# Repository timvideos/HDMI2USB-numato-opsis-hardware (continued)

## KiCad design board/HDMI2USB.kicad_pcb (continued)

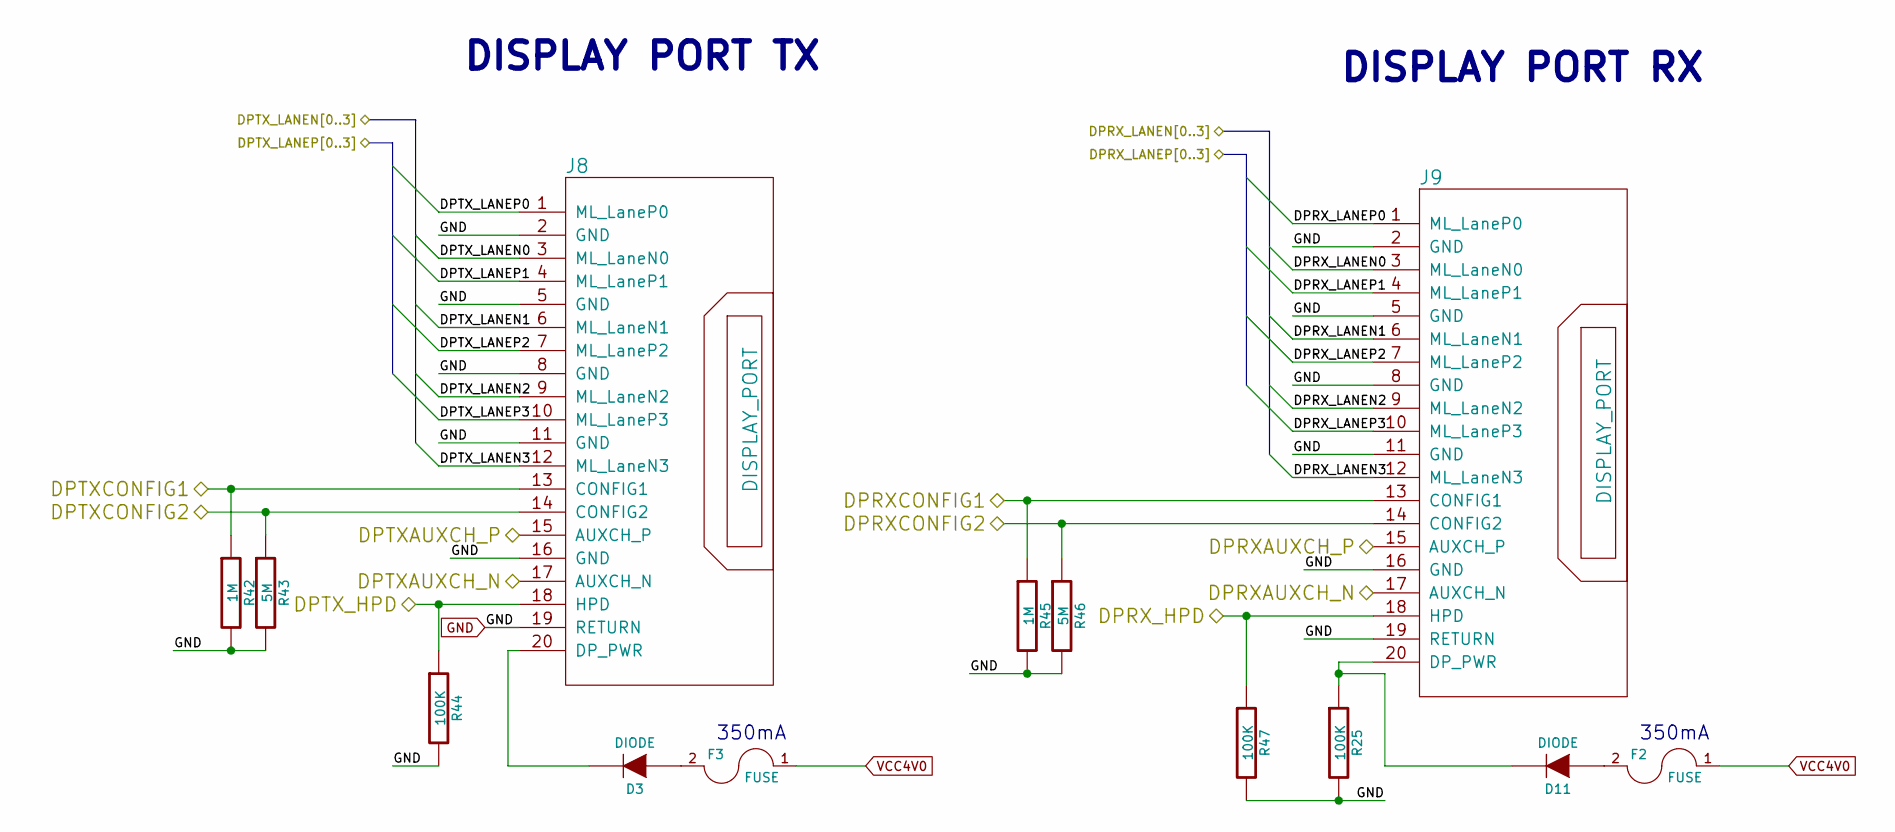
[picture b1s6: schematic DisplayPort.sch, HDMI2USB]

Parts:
D3, D11: DIODE
F2, F3: FUSE
J8, J9: DISPLAY_PORT
R25, R44, R47: 100K
R42, R45: 1M
R43, R46: 5M

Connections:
/DisplayPort/DPRXAUXCH_N: J9.17 (AUXCH_N); also elsewhere on the board
/DisplayPort/DPRXAUXCH_P: J9.15 (AUXCH_P); also elsewhere on the board
/DisplayPort/DPRXCONFIG1: J9.13 (CONFIG1), R45.1; also elsewhere on the board
/DisplayPort/DPRXCONFIG2: J9.14 (CONFIG2), R46.1; also elsewhere on the board
/DisplayPort/DPRX_LANEN0: J9.3 (ML_LaneN0); also elsewhere on the board
/DisplayPort/DPRX_LANEN1: J9.6 (ML_LaneN1); also elsewhere on the board
/DisplayPort/DPRX_LANEN2: J9.9 (ML_LaneN2); also elsewhere on the board
/DisplayPort/DPRX_LANEN3: J9.12 (ML_LaneN3); also elsewhere on the board
/DisplayPort/DPRX_LANEP0: J9.1 (ML_LaneP0); also elsewhere on the board
/DisplayPort/DPRX_LANEP1: J9.4 (ML_LaneP1); also elsewhere on the board
/DisplayPort/DPRX_LANEP2: J9.7 (ML_LaneP2); also elsewhere on the board
/DisplayPort/DPRX_LANEP3: J9.10 (ML_LaneP3); also elsewhere on the board
/DisplayPort/DPTXAUXCH_N: J8.17 (AUXCH_N); also elsewhere on the board
/DisplayPort/DPTXAUXCH_P: J8.15 (AUXCH_P); also elsewhere on the board
/DisplayPort/DPTXCONFIG1: J8.13 (CONFIG1), R42.1; also elsewhere on the board
/DisplayPort/DPTXCONFIG2: J8.14 (CONFIG2), R43.1; also elsewhere on the board
/DisplayPort/DPTX_LANEN0: J8.3 (ML_LaneN0); also elsewhere on the board
/DisplayPort/DPTX_LANEN1: J8.6 (ML_LaneN1); also elsewhere on the board
/DisplayPort/DPTX_LANEN2: J8.9 (ML_LaneN2); also elsewhere on the board
/DisplayPort/DPTX_LANEN3: J8.12 (ML_LaneN3); also elsewhere on the board
/DisplayPort/DPTX_LANEP0: J8.1 (ML_LaneP0); also elsewhere on the board
/DisplayPort/DPTX_LANEP1: J8.4 (ML_LaneP1); also elsewhere on the board
/DisplayPort/DPTX_LANEP2: J8.7 (ML_LaneP2); also elsewhere on the board
/DisplayPort/DPTX_LANEP3: J8.10 (ML_LaneP3); also elsewhere on the board
/FPGA_Bank_1_2/DPRXHPD: J9.18 (HPD), R47.1; also elsewhere on the board
/FPGA_Bank_1_2/DPTXHPD: J8.18 (HPD), R44.1; also elsewhere on the board
unnamed: D11.2 (K), J9.20 (DP_PWR), R25.1
unnamed: D3.1 (A), F3.2
unnamed: D3.2 (K), J8.20 (DP_PWR)

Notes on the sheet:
350mA
DISPLAY PORT TX
DISPLAY PORT RX

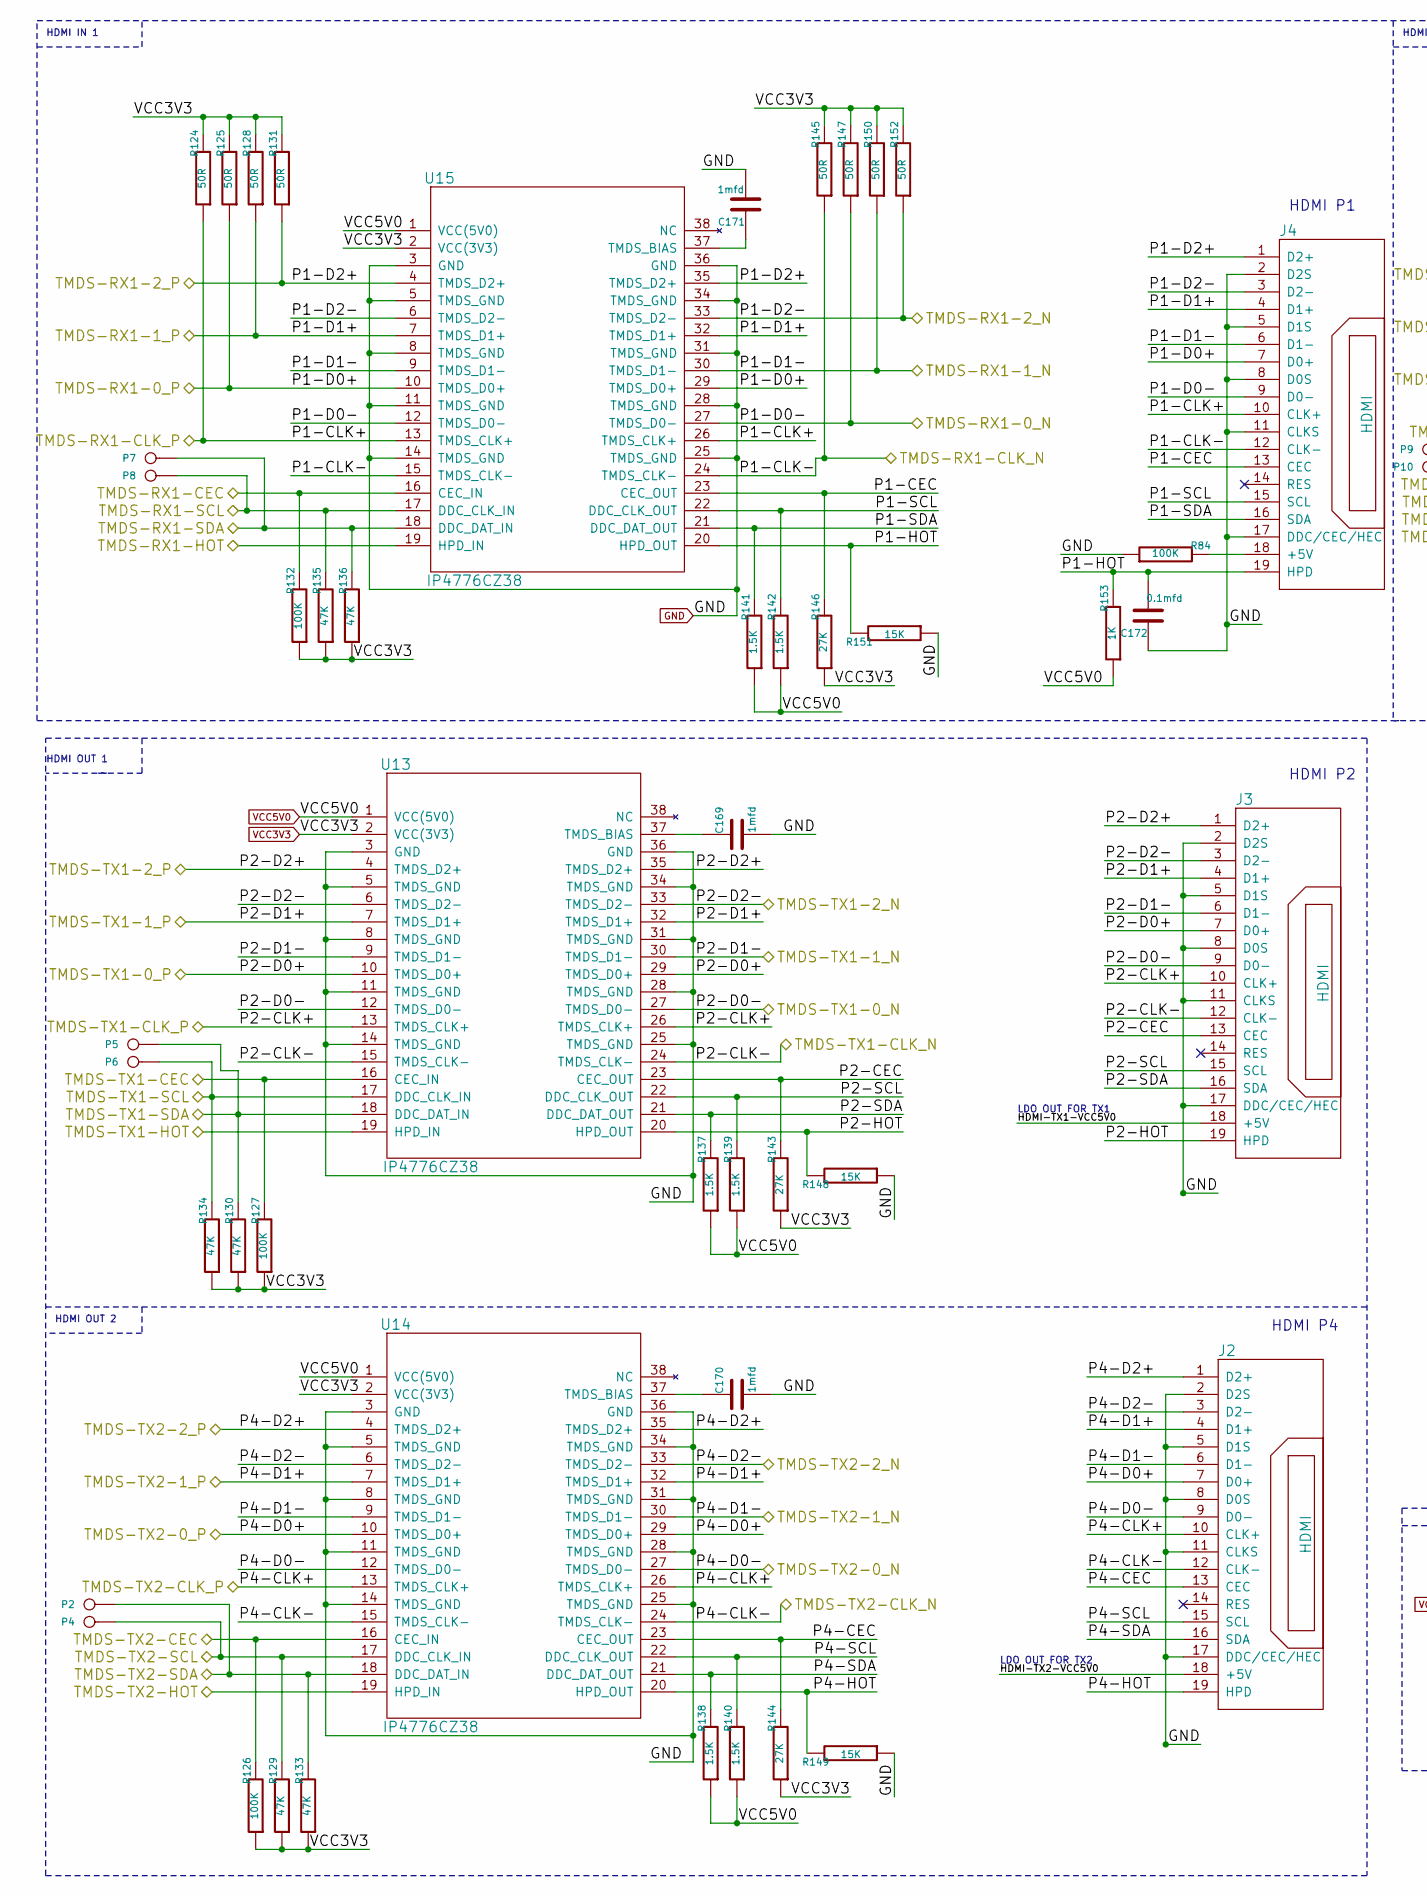
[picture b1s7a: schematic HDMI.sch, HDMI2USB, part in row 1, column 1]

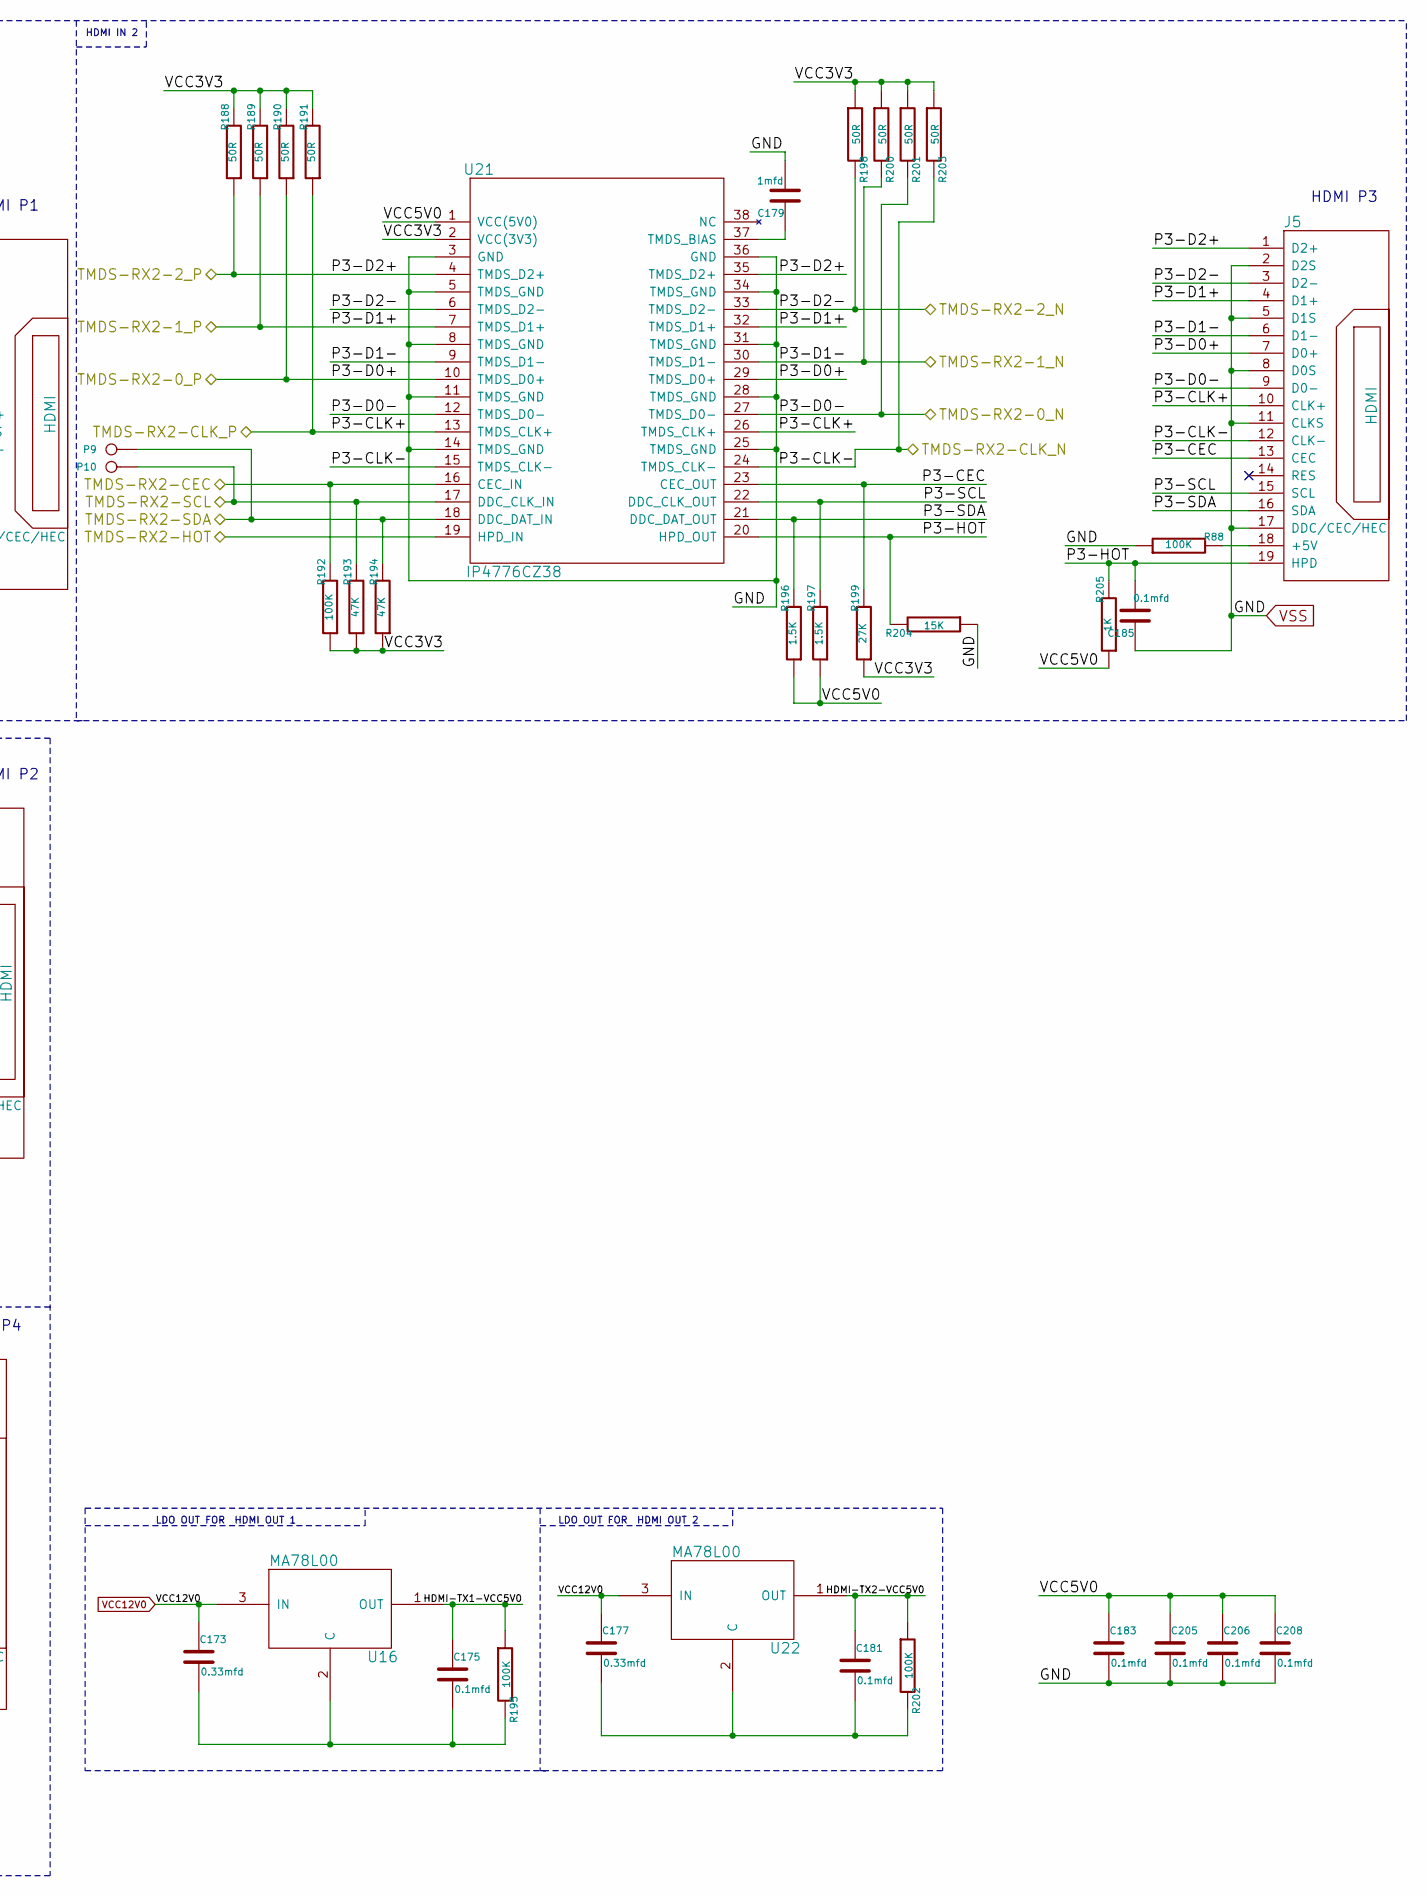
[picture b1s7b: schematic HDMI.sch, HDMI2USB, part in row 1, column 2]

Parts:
C169, C170, C171, C179: 1mfd
C172, C175, C181, C183, C185, C205, C206, C208: 0.1mfd
C173, C177: 0.33mfd
J2, J3, J4, J5: HDMI
P2, P4, P5, P6, P7, P8, P9, P10: CONN_1
R84, R88, R126, R127, R132, R192, R195, R202: 100K
R124, R125, R128, R131, R145, R147, R150, R152, R188, R189, R190, R191, R198, R200, R201, R203: 50R
R129, R130, R133, R134, R135, R136, R193, R194: 47K
R137, R138, R139, R140, R141, R142, R196, R197: 1.5K
R143, R144, R146, R199: 27K
R148, R149, R151, R204: 15K
R153, R205: 1K
U13, U14, U15, U21: IP4776CZ38
U16, U22: ΜA78L00

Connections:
/HDMI/HDMI-TX1-VCC5V0: C175.1, J3.18 (+5V), R195.1, U16.1 (OUT)
/HDMI/HDMI-TX2-VCC5V0: C181.1, J2.18 (+5V), R202.1, U22.1 (OUT)
/HDMI/P1-CEC: J4.13 (CEC), R146.2, U15.23 (CEC_OUT)
/HDMI/P1-HOT: C172.2, J4.19 (HPD), R151.2, R153.2, U15.20 (HPD_OUT)
/HDMI/P1-SCL: J4.15 (SCL), R142.2, U15.22 (DDC_CLK_OUT)
/HDMI/P1-SDA: J4.16 (SDA), R141.2, U15.21 (DDC_DAT_OUT)
/HDMI/P2-CEC: J3.13 (CEC), R143.2, U13.23 (CEC_OUT)
/HDMI/P2-HOT: J3.19 (HPD), R148.2, U13.20 (HPD_OUT)
/HDMI/P2-SCL: J3.15 (SCL), R139.2, U13.22 (DDC_CLK_OUT)
/HDMI/P2-SDA: J3.16 (SDA), R137.2, U13.21 (DDC_DAT_OUT)
/HDMI/P3-CEC: J5.13 (CEC), R199.2, U21.23 (CEC_OUT)
/HDMI/P3-HOT: C185.2, J5.19 (HPD), R204.2, R205.2, U21.20 (HPD_OUT)
/HDMI/P3-SCL: J5.15 (SCL), R197.2, U21.22 (DDC_CLK_OUT)
/HDMI/P3-SDA: J5.16 (SDA), R196.2, U21.21 (DDC_DAT_OUT)
/HDMI/P4-CEC: J2.13 (CEC), R144.2, U14.23 (CEC_OUT)
/HDMI/P4-HOT: J2.19 (HPD), R149.2, U14.20 (HPD_OUT)
/HDMI/P4-SCL: J2.15 (SCL), R140.2, U14.22 (DDC_CLK_OUT)
/HDMI/P4-SDA: J2.16 (SDA), R138.2, U14.21 (DDC_DAT_OUT)
/HDMI/TMDS-RX1-0_N: J4.9 (D0-), R147.1, U15.12 (TMDS_D0-), U15.27 (TMDS_D0-); also elsewhere on the board
/HDMI/TMDS-RX1-0_P: J4.7 (D0+), R125.1, U15.10 (TMDS_D0+), U15.29 (TMDS_D0+); also elsewhere on the board
/HDMI/TMDS-RX1-1_N: J4.6 (D1-), R150.1, U15.9 (TMDS_D1-), U15.30 (TMDS_D1-); also elsewhere on the board
/HDMI/TMDS-RX1-1_P: J4.4 (D1+), R128.1, U15.7 (TMDS_D1+), U15.32 (TMDS_D1+); also elsewhere on the board
/HDMI/TMDS-RX1-2_N: J4.3 (D2-), R152.1, U15.6 (TMDS_D2-), U15.33 (TMDS_D2-); also elsewhere on the board
/HDMI/TMDS-RX1-2_P: J4.1 (D2+), R131.1, U15.4 (TMDS_D2+), U15.35 (TMDS_D2+); also elsewhere on the board
/HDMI/TMDS-RX1-CEC: R132.2, U15.16 (CEC_IN); also elsewhere on the board
/HDMI/TMDS-RX1-CLK_N: J4.12 (CLK-), R145.1, U15.15 (TMDS_CLK-), U15.24 (TMDS_CLK-); also elsewhere on the board
/HDMI/TMDS-RX1-CLK_P: J4.10 (CLK+), R124.1, U15.13 (TMDS_CLK+), U15.26 (TMDS_CLK+); also elsewhere on the board
/HDMI/TMDS-RX1-HOT: U15.19 (HPD_IN); also elsewhere on the board
/HDMI/TMDS-RX1-SCL: P8.1, R135.2, U15.17 (DDC_CLK_IN); also elsewhere on the board
/HDMI/TMDS-RX1-SDA: P7.1, R136.2, U15.18 (DDC_DAT_IN); also elsewhere on the board
/HDMI/TMDS-RX2-0_N: J5.9 (D0-), R201.2, U21.12 (TMDS_D0-), U21.27 (TMDS_D0-); also elsewhere on the board
/HDMI/TMDS-RX2-0_P: J5.7 (D0+), R190.1, U21.10 (TMDS_D0+), U21.29 (TMDS_D0+); also elsewhere on the board
/HDMI/TMDS-RX2-1_N: J5.6 (D1-), R200.2, U21.9 (TMDS_D1-), U21.30 (TMDS_D1-); also elsewhere on the board
/HDMI/TMDS-RX2-1_P: J5.4 (D1+), R189.1, U21.7 (TMDS_D1+), U21.32 (TMDS_D1+); also elsewhere on the board
/HDMI/TMDS-RX2-2_N: J5.3 (D2-), R198.2, U21.6 (TMDS_D2-), U21.33 (TMDS_D2-); also elsewhere on the board
/HDMI/TMDS-RX2-2_P: J5.1 (D2+), R188.1, U21.4 (TMDS_D2+), U21.35 (TMDS_D2+); also elsewhere on the board
/HDMI/TMDS-RX2-CEC: R192.2, U21.16 (CEC_IN); also elsewhere on the board
/HDMI/TMDS-RX2-CLK_N: J5.12 (CLK-), R203.2, U21.15 (TMDS_CLK-), U21.24 (TMDS_CLK-); also elsewhere on the board
/HDMI/TMDS-RX2-CLK_P: J5.10 (CLK+), R191.1, U21.13 (TMDS_CLK+), U21.26 (TMDS_CLK+); also elsewhere on the board
/HDMI/TMDS-RX2-HOT: U21.19 (HPD_IN); also elsewhere on the board
/HDMI/TMDS-RX2-SCL: P10.1, R193.2, U21.17 (DDC_CLK_IN); also elsewhere on the board
/HDMI/TMDS-RX2-SDA: P9.1, R194.2, U21.18 (DDC_DAT_IN); also elsewhere on the board
/HDMI/TMDS-TX1-0_N: J3.9 (D0-), U13.12 (TMDS_D0-), U13.27 (TMDS_D0-); also elsewhere on the board
/HDMI/TMDS-TX1-0_P: J3.7 (D0+), U13.10 (TMDS_D0+), U13.29 (TMDS_D0+); also elsewhere on the board
/HDMI/TMDS-TX1-1_N: J3.6 (D1-), U13.9 (TMDS_D1-), U13.30 (TMDS_D1-); also elsewhere on the board
/HDMI/TMDS-TX1-1_P: J3.4 (D1+), U13.7 (TMDS_D1+), U13.32 (TMDS_D1+); also elsewhere on the board
/HDMI/TMDS-TX1-2_N: J3.3 (D2-), U13.6 (TMDS_D2-), U13.33 (TMDS_D2-); also elsewhere on the board
/HDMI/TMDS-TX1-2_P: J3.1 (D2+), U13.4 (TMDS_D2+), U13.35 (TMDS_D2+); also elsewhere on the board
/HDMI/TMDS-TX1-CEC: R127.2, U13.16 (CEC_IN); also elsewhere on the board
/HDMI/TMDS-TX1-CLK_N: J3.12 (CLK-), U13.15 (TMDS_CLK-), U13.24 (TMDS_CLK-); also elsewhere on the board
/HDMI/TMDS-TX1-CLK_P: J3.10 (CLK+), U13.13 (TMDS_CLK+), U13.26 (TMDS_CLK+); also elsewhere on the board
/HDMI/TMDS-TX1-HOT: U13.19 (HPD_IN); also elsewhere on the board
/HDMI/TMDS-TX1-SCL: P6.1, R134.2, U13.17 (DDC_CLK_IN); also elsewhere on the board
/HDMI/TMDS-TX1-SDA: P5.1, R130.2, U13.18 (DDC_DAT_IN); also elsewhere on the board
/HDMI/TMDS-TX2-0_N: J2.9 (D0-), U14.12 (TMDS_D0-), U14.27 (TMDS_D0-); also elsewhere on the board
/HDMI/TMDS-TX2-0_P: J2.7 (D0+), U14.10 (TMDS_D0+), U14.29 (TMDS_D0+); also elsewhere on the board
/HDMI/TMDS-TX2-1_N: J2.6 (D1-), U14.9 (TMDS_D1-), U14.30 (TMDS_D1-); also elsewhere on the board
/HDMI/TMDS-TX2-1_P: J2.4 (D1+), U14.7 (TMDS_D1+), U14.32 (TMDS_D1+); also elsewhere on the board
/HDMI/TMDS-TX2-2_N: J2.3 (D2-), U14.6 (TMDS_D2-), U14.33 (TMDS_D2-); also elsewhere on the board
/HDMI/TMDS-TX2-2_P: J2.1 (D2+), U14.4 (TMDS_D2+), U14.35 (TMDS_D2+); also elsewhere on the board
/HDMI/TMDS-TX2-CEC: R126.2, U14.16 (CEC_IN); also elsewhere on the board
/HDMI/TMDS-TX2-CLK_N: J2.12 (CLK-), U14.15 (TMDS_CLK-), U14.24 (TMDS_CLK-); also elsewhere on the board
/HDMI/TMDS-TX2-CLK_P: J2.10 (CLK+), U14.13 (TMDS_CLK+), U14.26 (TMDS_CLK+); also elsewhere on the board
/HDMI/TMDS-TX2-HOT: U14.19 (HPD_IN); also elsewhere on the board
/HDMI/TMDS-TX2-SCL: P4.1, R129.2, U14.17 (DDC_CLK_IN); also elsewhere on the board
/HDMI/TMDS-TX2-SDA: P2.1, R133.2, U14.18 (DDC_DAT_IN); also elsewhere on the board
unnamed: J4.18 (+5V), R84.2
unnamed: C173.2, C175.2, R195.2, U16.2 (C)
unnamed: C170.1, U14.37 (TMDS_BIAS)
unnamed: C169.1, U13.37 (TMDS_BIAS)
unnamed: C171.1, U15.37 (TMDS_BIAS)
unnamed: J5.18 (+5V), R88.2
unnamed: C179.1, U21.37 (TMDS_BIAS)
unnamed: C177.2, C181.2, R202.2, U22.2 (C)
VCC5V0: C183.1, C205.1, C206.1, C208.1, R137.1, R138.1, R139.1, R140.1, R141.1, R142.1, R153.1, R196.1, R197.1, R205.1, U13.1 (VCC(5V0)), U14.1 (VCC(5V0)), U15.1 (VCC(5V0)), U21.1 (VCC(5V0)); also elsewhere on the board
VCC12V0: C173.1, C177.1, U16.3 (IN), U22.3 (IN); also elsewhere on the board

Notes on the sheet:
HDMI P1
HDMI P2
HDMI P4
HDMI P3
HDMI IN 1
HDMI OUT 1
LDO OUT FOR
LDO OUT FOR TX1
LDO OUT FOR TX2
HDMI OUT 2
HDMI IN 2

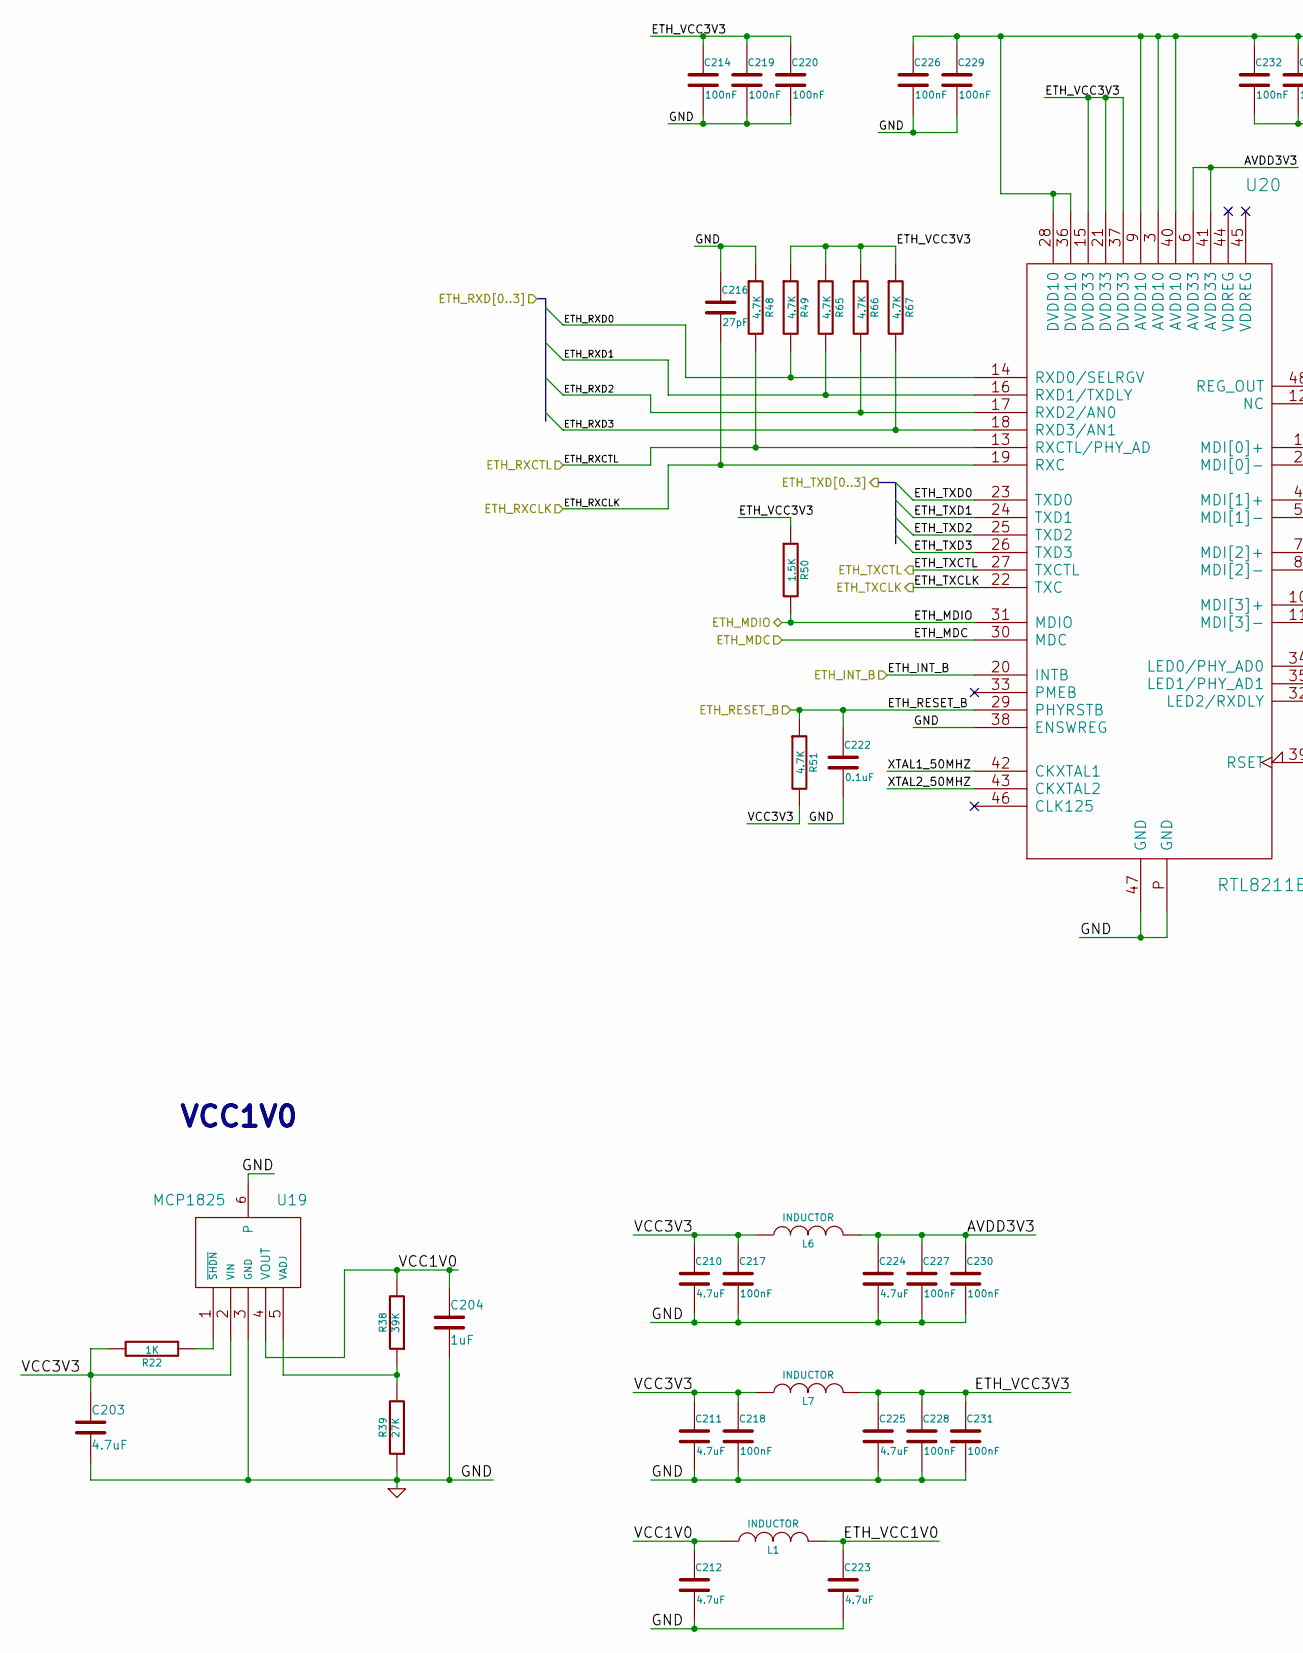
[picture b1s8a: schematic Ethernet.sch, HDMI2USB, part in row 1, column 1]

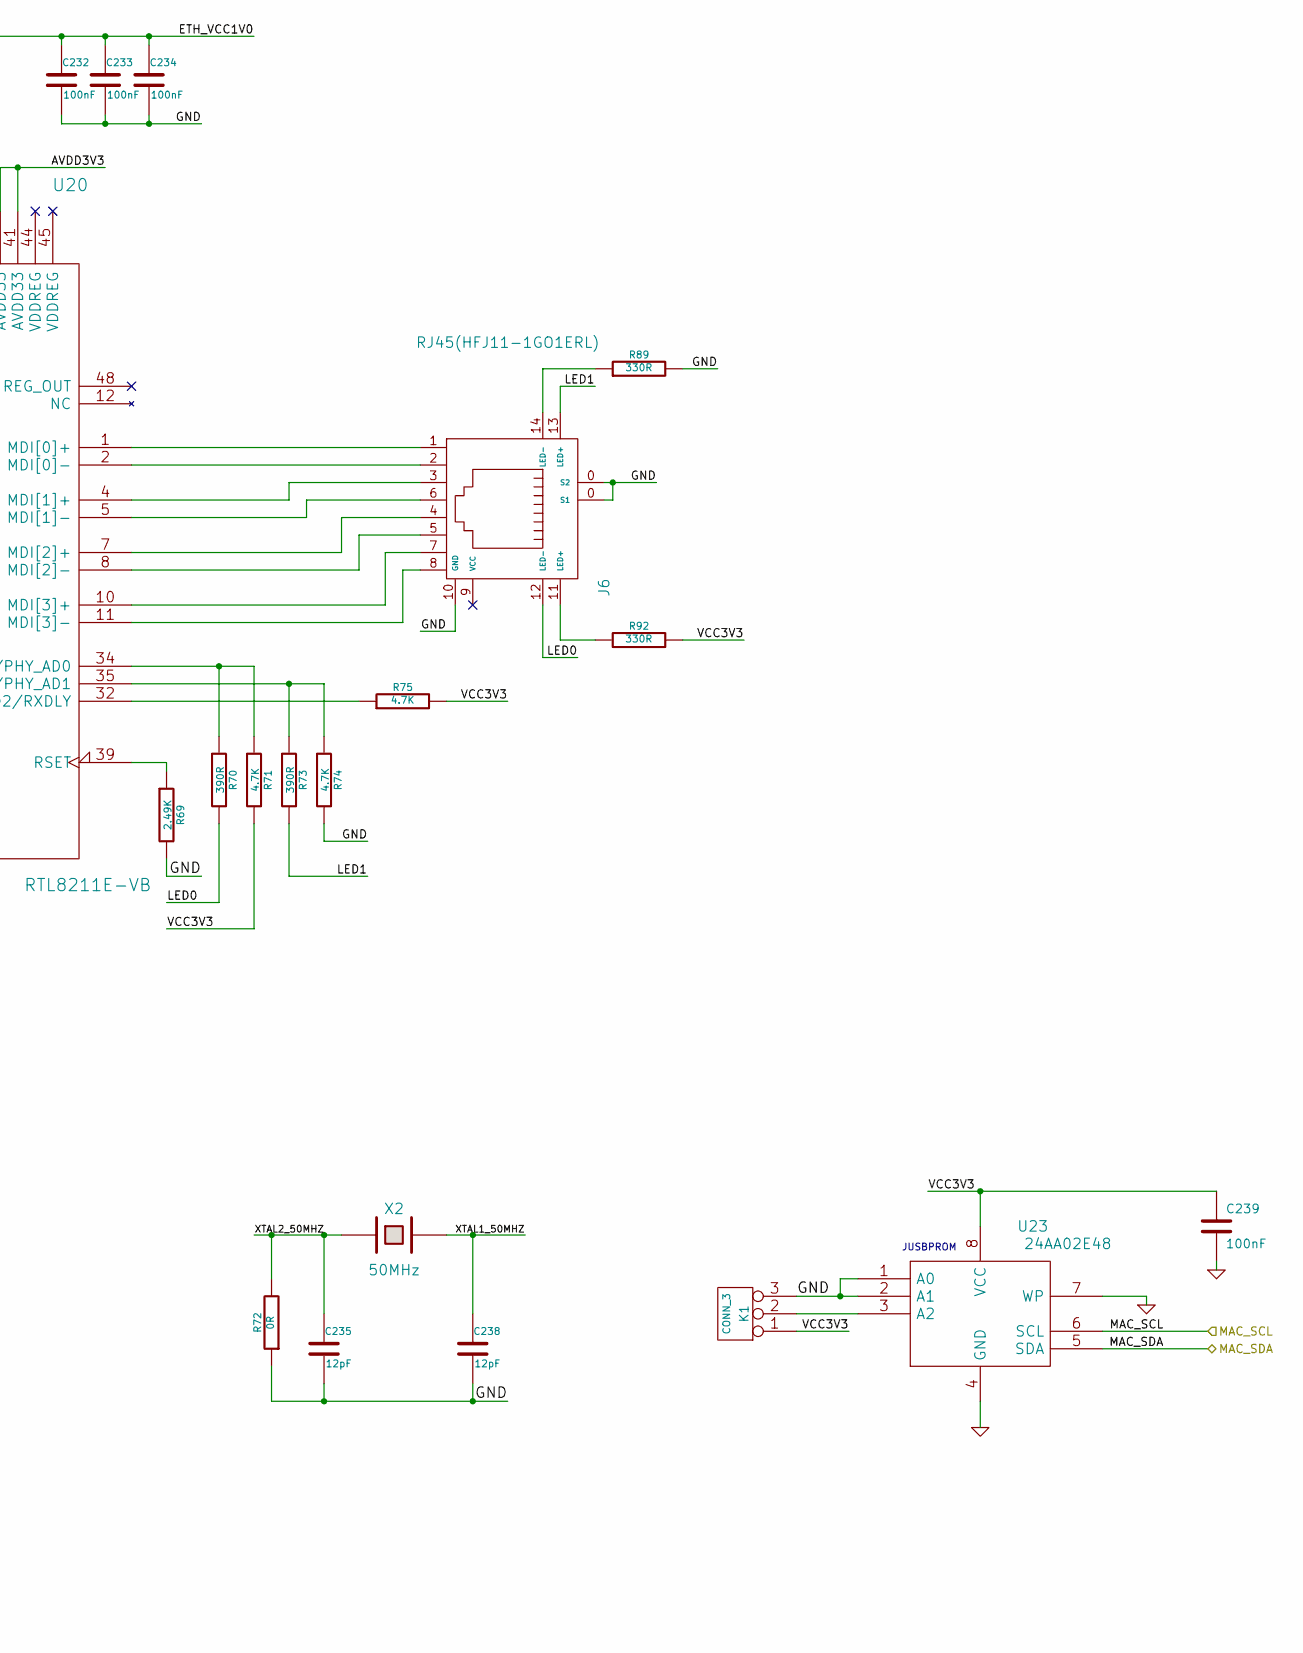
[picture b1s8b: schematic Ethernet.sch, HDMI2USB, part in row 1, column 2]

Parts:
C203: 4.7uF
C204: 1uF
C210, C211, C212, C223, C224, C225: 4.7uF
C214, C217, C218, C219, C220, C226, C227, C228, C229, C230, C231, C232, C233, C234: 100nF
C216: 27pF
C222: 0.1uF
C235, C238: 12pF
C239: 100nF; SM0805
J6: RJ45(HFJ11-1GO1ERL)
K1: CONN_3
L1, L6, L7: INDUCTOR
R22: 1K
R38: 39K
R39: 27K
R48, R49, R51, R65, R66, R67, R71, R74, R75: 4.7K
R50: 1.5K
R69: 2.49K
R70, R73: 390R
R72: 0R
R89, R92: 330R
U19: MCP1825
U20: RTL8211E-VB
U23: 24AA02E48; SO8
X2: 50MHz

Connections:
/Ethernet/AVDD3V3: C224.1, C227.1, C230.1, L6.2, U20.6 (AVDD33), U20.41 (AVDD33)
/Ethernet/ETH_INT_B: U20.20 (INTB); also elsewhere on the board
/Ethernet/ETH_MDC: U20.30 (MDC); also elsewhere on the board
/Ethernet/ETH_MDIO: R50.2, U20.31 (MDIO); also elsewhere on the board
/Ethernet/ETH_RESET_B: C222.1, R51.1, U20.29 (PHYRSTB); also elsewhere on the board
/Ethernet/ETH_RXCLK: C216.2, U20.19 (RXC); also elsewhere on the board
/Ethernet/ETH_RXCTL: R48.2, U20.13 (RXCTL/PHY_AD); also elsewhere on the board
/Ethernet/ETH_RXD0: R49.2, U20.14 (RXD0/SELRGV); also elsewhere on the board
/Ethernet/ETH_RXD1: R65.2, U20.16 (RXD1/TXDLY); also elsewhere on the board
/Ethernet/ETH_RXD2: R66.2, U20.17 (RXD2/AN0); also elsewhere on the board
/Ethernet/ETH_RXD3: R67.2, U20.18 (RXD3/AN1); also elsewhere on the board
/Ethernet/ETH_TXCLK: U20.22 (TXC); also elsewhere on the board
/Ethernet/ETH_TXCTL: U20.27 (TXCTL); also elsewhere on the board
/Ethernet/ETH_TXD0: U20.23 (TXD0); also elsewhere on the board
/Ethernet/ETH_TXD1: U20.24 (TXD1); also elsewhere on the board
/Ethernet/ETH_TXD2: U20.25 (TXD2); also elsewhere on the board
/Ethernet/ETH_TXD3: U20.26 (TXD3); also elsewhere on the board
/Ethernet/ETH_VCC1V0: C223.1, C226.1, C229.1, C232.1, C233.1, C234.1, L1.2, U20.3 (AVDD10), U20.9 (AVDD10), U20.28 (DVDD10), U20.36 (DVDD10), U20.40 (AVDD10)
/Ethernet/ETH_VCC3V3: C214.1, C219.1, C220.1, C225.1, C228.1, C231.1, L7.2, R49.1, R50.1, R65.1, R66.1, R67.1, U20.15 (DVDD33), U20.21 (DVDD33), U20.37 (DVDD33)
/Ethernet/LED0: J6.12 (LED-), R70.2
/Ethernet/LED1: J6.13 (LED+), R73.2
/Ethernet/MAC_SDA: U23.5 (SDA); also elsewhere on the board
/Ethernet/VCC1V0: C204.1, C212.1, L1.1, R38.2, U19.4 (VOUT)
/Ethernet/VCC3V3: C203.1, C210.1, C211.1, C217.1, C218.1, C239.1, K1.1, L6.1, L7.1, R22.2, R51.2, R71.2, R75.2, R92.2, U19.2 (VIN), U23.8 (VCC); also elsewhere on the board
/Ethernet/XTAL1_50MHZ: C238.1, U20.42 (CKXTAL1), X2.2; also elsewhere on the board
/Ethernet/XTAL2_50MHZ: C235.1, R72.2, U20.43 (CKXTAL2), X2.1
unnamed: J6.2, U20.2 (MDI[0]-)
unnamed: J6.3, U20.4 (MDI[1]+)
unnamed: J6.6, U20.5 (MDI[1]-)
unnamed: J6.4, U20.7 (MDI[2]+)
unnamed: J6.1, U20.1 (MDI[0]+)
unnamed: J6.5, U20.8 (MDI[2]-)
unnamed: J6.7, U20.10 (MDI[3]+)
unnamed: J6.8, U20.11 (MDI[3]-)
unnamed: K1.2 (PM), U23.3 (A2)
unnamed: R75.1, U20.32 (LED2/RXDLY)
unnamed: R73.1, R74.1, U20.35 (LED1/PHY_AD1)
unnamed: R69.1, U20.39 (RSET)
unnamed: R70.1, R71.1, U20.34 (LED0/PHY_AD0)
unnamed: R22.1, U19.1 (~SHDN)
unnamed: R38.1, R39.2, U19.5 (VADJ)
unnamed: J6.11 (LED+), R92.1
unnamed: J6.14 (LED-), R89.1

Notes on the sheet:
VCC1V0
JUSBPROM

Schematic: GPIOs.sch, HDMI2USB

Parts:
U25: TIMVIDEOS-PCIE-8X

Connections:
/FPGA_Bank_0_3/DIFFCLK_A0N: U25.A30 (DIFF_CLK_A0N); also elsewhere on the board
/FPGA_Bank_0_3/DIFFCLK_A0P: U25.A29 (DIFF_CLK_A0P); also elsewhere on the board
/FPGA_Bank_0_3/DIFFCLK_A1N: U25.A48 (DIFF_CLK_A1N); also elsewhere on the board
/FPGA_Bank_0_3/DIFFCLK_A1P: U25.A47 (DIFF_CLK_A1P); also elsewhere on the board
/FPGA_Bank_0_3/DIFFCLK_B0N: U25.B28 (DIFF_CLK_B0N); also elsewhere on the board
/FPGA_Bank_0_3/DIFFCLK_B0P: U25.B27 (DIFF_CLK_B0P); also elsewhere on the board
/FPGA_Bank_0_3/DIFFCLK_B1N: U25.B46 (DIFF_CLK_B1N); also elsewhere on the board
/FPGA_Bank_0_3/DIFFCLK_B1P: U25.B45 (DIFF_CLK_B1P); also elsewhere on the board
/FPGA_Bank_0_3/DIFFCLK_XN: U25.A14 (DIFF_CLK_XN); also elsewhere on the board
/FPGA_Bank_0_3/DIFFCLK_XP: U25.A13 (DIFF_CLK_XP); also elsewhere on the board
/FPGA_Bank_0_3/DIFFIO_A0N: U25.A6 (DIFF_IO_A0N); also elsewhere on the board
/FPGA_Bank_0_3/DIFFIO_A0P: U25.A5 (DIFF_IO_A0P); also elsewhere on the board
/FPGA_Bank_0_3/DIFFIO_A1N: U25.A17 (DIFF_IO_A1N); also elsewhere on the board
/FPGA_Bank_0_3/DIFFIO_A1P: U25.A16 (DIFF_IO_A1P); also elsewhere on the board
/FPGA_Bank_0_3/DIFFIO_A2N: U25.A22 (DIFF_IO_A2N); also elsewhere on the board
/FPGA_Bank_0_3/DIFFIO_A2P: U25.A21 (DIFF_IO_A2P); also elsewhere on the board
/FPGA_Bank_0_3/DIFFIO_A3N: U25.A26 (DIFF_IO_A3N); also elsewhere on the board
/FPGA_Bank_0_3/DIFFIO_A3P: U25.A25 (DIFF_IO_A3P); also elsewhere on the board
/FPGA_Bank_0_3/DIFFIO_A4N: U25.A36 (DIFF_IO_A4N); also elsewhere on the board
/FPGA_Bank_0_3/DIFFIO_A4P: U25.A35 (DIFF_IO_A4P); also elsewhere on the board
/FPGA_Bank_0_3/DIFFIO_A5N: U25.A40 (DIFF_IO_A5N); also elsewhere on the board
/FPGA_Bank_0_3/DIFFIO_A5P: U25.A39 (DIFF_IO_A5P); also elsewhere on the board
/FPGA_Bank_0_3/DIFFIO_A6N: U25.A44 (DIFF_IO_A6N); also elsewhere on the board
/FPGA_Bank_0_3/DIFFIO_A6P: U25.A43 (DIFF_IO_A6P); also elsewhere on the board
/FPGA_Bank_0_3/DIFFIO_B0N: U25.A8 (DIFF_IO_B0N); also elsewhere on the board
/FPGA_Bank_0_3/DIFFIO_B0P: U25.A7 (DIFF_IO_B0P); also elsewhere on the board
/FPGA_Bank_0_3/DIFFIO_B1N: U25.B15 (DIFF_IO_B1N); also elsewhere on the board
/FPGA_Bank_0_3/DIFFIO_B1P: U25.B14 (DIFF_IO_B1P); also elsewhere on the board
/FPGA_Bank_0_3/DIFFIO_B2N: U25.B20 (DIFF_IO_B2N); also elsewhere on the board
/FPGA_Bank_0_3/DIFFIO_B2P: U25.B19 (DIFF_IO_B2P); also elsewhere on the board
/FPGA_Bank_0_3/DIFFIO_B3N: U25.B24 (DIFF_IO_B3N); also elsewhere on the board
/FPGA_Bank_0_3/DIFFIO_B3P: U25.B23 (DIFF_IO_B3P); also elsewhere on the board
/FPGA_Bank_0_3/DIFFIO_B4N: U25.B34 (DIFF_IO_B4N); also elsewhere on the board
/FPGA_Bank_0_3/DIFFIO_B4P: U25.B33 (DIFF_IO_B4P); also elsewhere on the board
/FPGA_Bank_0_3/DIFFIO_B5N: U25.B38 (DIFF_IO_B5N); also elsewhere on the board
/FPGA_Bank_0_3/DIFFIO_B5P: U25.B37 (DIFF_IO_B5P); also elsewhere on the board
/FPGA_Bank_0_3/DIFFIO_B6N: U25.B42 (DIFF_IO_B6N); also elsewhere on the board
/FPGA_Bank_0_3/DIFFIO_B6P: U25.B41 (DIFF_IO_B6P); also elsewhere on the board
/FPGA_Bank_0_3/DIFFIO_XN: U25.B11 (DIFF_IO_XN); also elsewhere on the board
/FPGA_Bank_0_3/DIFFIO_XP: U25.B9 (DIFF_IO_XP); also elsewhere on the board
/FPGA_Bank_0_3/DIFFIO_YN: U25.B12 (DIFF_IO_YN); also elsewhere on the board
/FPGA_Bank_0_3/DIFFIO_YP: U25.A19 (DIFF_IO_YP); also elsewhere on the board
/FPGA_Bank_0_3/DIFFIO_ZN: U25.B30 (DIFF_IO_ZN); also elsewhere on the board
/FPGA_Bank_0_3/DIFFIO_ZP: U25.A32 (DIFF_IO_ZP); also elsewhere on the board
/FPGA_Bank_0_3/PCIE_RESET: U25.A11 (~RST); also elsewhere on the board
/GPIOs/PRSNT: U25.A1 (~PRSNT1), U25.B17 (~PRSNT2), U25.B31 (~PRSNT2), U25.B48 (~PRSNT2)
VCC12V0: U25.A2 (12V), U25.A3 (12V), U25.B1 (12V), U25.B2 (12V), U25.B3 (12V); also elsewhere on the board

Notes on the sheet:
PCIe
